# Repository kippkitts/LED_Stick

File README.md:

LED_Stick
=========

The LED Stick contains eight white LEDs and an AS1109 8-Bit LED driver, which allows you to control the states of all the LEDs with just two data pins from a microcontroller.  Eagle files for the board are provided here, as are an Arduino sketch and a Processing based graphical user interface for selecting and displaying custom flash patterns.   

###Graphical User Interface

The GUI will display 64 gray circles.  The 8 circles in each row represent the 8 LEDs on the circuit board.  Clicking on the circles will toggle the state of the corresponding LEDs on the Stick.  Once you've selected a pattern on each row, the Processing sketch will cycle through the rows (top to bottom) and display them on the LED Stick one after the other at 75 ms intervals.

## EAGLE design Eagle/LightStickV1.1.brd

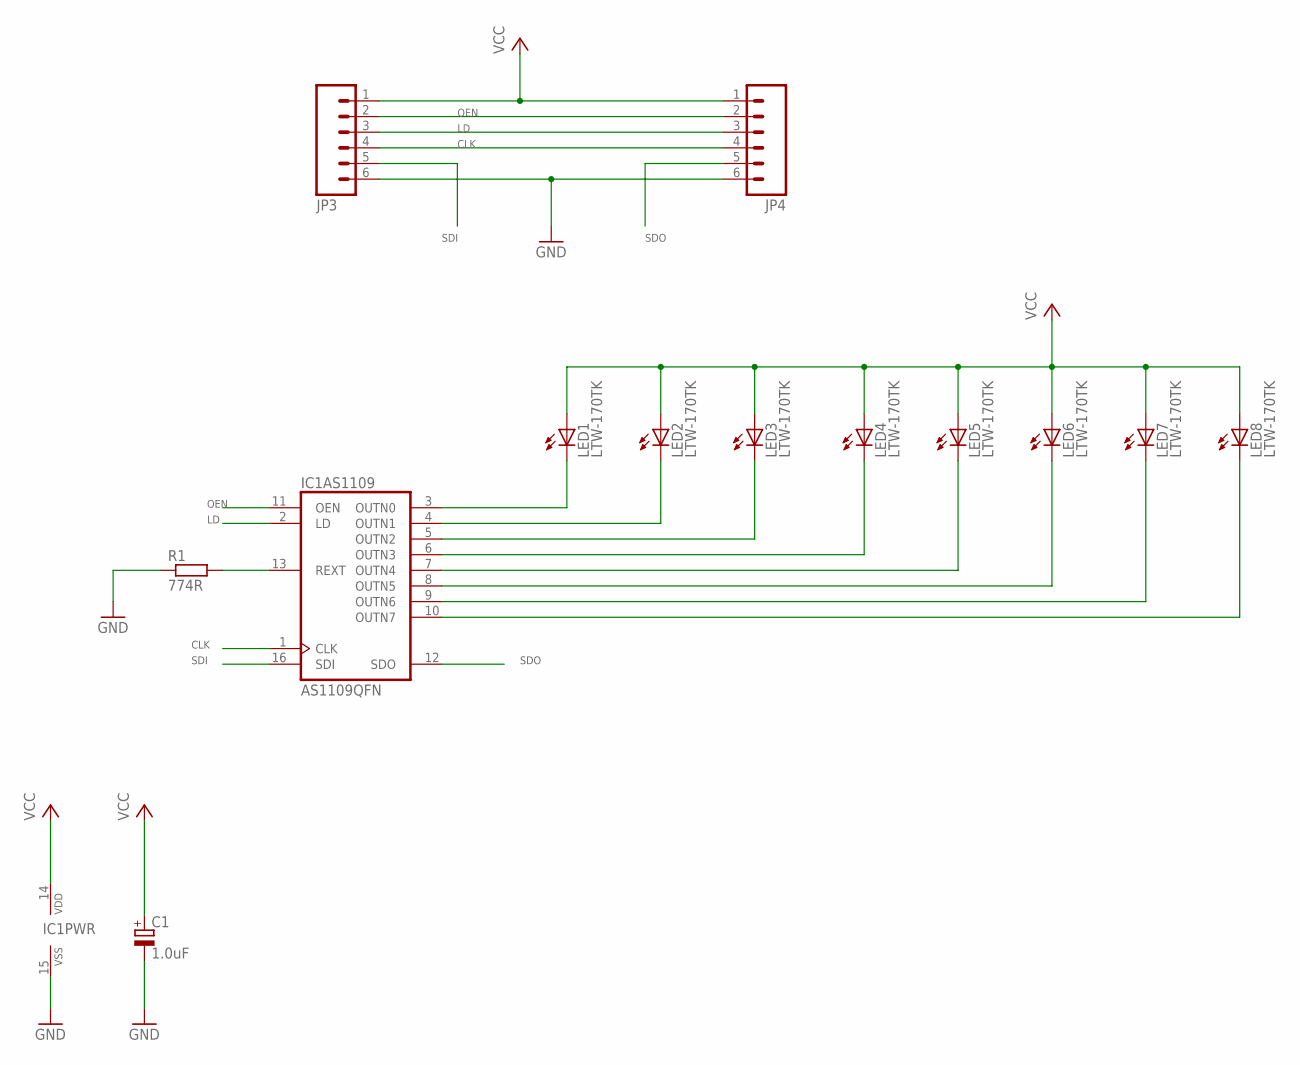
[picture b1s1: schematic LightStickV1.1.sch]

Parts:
C1: 1.0uF; SMC_B
IC1: AS1109QFN; QFN16-HS
JP3, JP4: M06LOCK; 1X06_LOCK
LED1, LED2, LED3, LED4, LED5, LED6, LED7, LED8: LTW-170TK; CHIPLED_0805
R1: 774R; R0805

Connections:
CLK: IC1.1 (CLK), JP3.4, JP4.4
GND: C1.-, IC1.15 (VSS), JP3.6, JP4.6, R1.1
LD: IC1.2 (LD), JP3.3, JP4.3
unnamed: IC1.3 (OUTN0), LED1.C
unnamed: IC1.4 (OUTN1), LED2.C
unnamed: IC1.5 (OUTN2), LED3.C
unnamed: IC1.6 (OUTN3), LED4.C
unnamed: IC1.7 (OUTN4), LED5.C
unnamed: IC1.8 (OUTN5), LED6.C
unnamed: IC1.13 (REXT), R1.2
unnamed: IC1.9 (OUTN6), LED7.C
unnamed: IC1.10 (OUTN7), LED8.C
OEN: IC1.11 (OEN), JP3.2, JP4.2
SDI: IC1.16 (SDI), JP3.5
SDO: IC1.12 (SDO), JP4.5
VCC: C1.+, IC1.14 (VDD), JP3.1, JP4.1, LED1.A, LED2.A, LED3.A, LED4.A, LED5.A, LED6.A, LED7.A, LED8.A

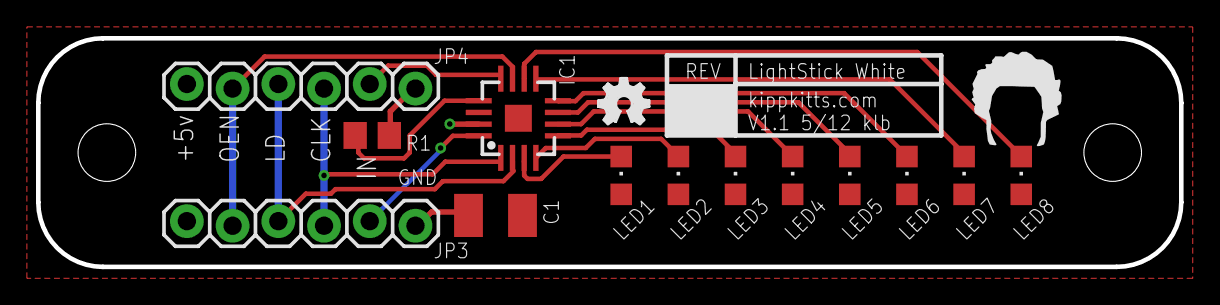
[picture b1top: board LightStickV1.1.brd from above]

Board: 2 copper layers, 63.5 x 12.7 mm, 16 parts (0 on the bottom side), 16 nets.

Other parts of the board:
DRILEGEND: DRILEGEND
U$1: TOP_DOCU_5MM
U$2: OSHW_FILLX100_NOTEXT

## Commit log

2014-03-26 Create Repository
